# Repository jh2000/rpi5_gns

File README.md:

# RPi5 HAT+ for GNS AIS and ADS-B Modules

# Aktuelle Fehler
- Im aktuellen Layout ist ein Kreuzungsfehler, dadurch wird UART_Rx an Pin 10 vom GNS5851 mit F_ind verbunden.  
Wird die Platine so gefertigt, muss die Verbindung aufgetrennt werden (direkt vor dem GNS5851, zum Glück sehr gut erreichbar) und manuell eine Brücke von Pin 5 zu R7 gelegt werden.
- Der RX-Pin vom AIS-Modul ist mit GPIO 7 anstelle 8 verbunden, daher ist keine Kommunikation vom RPi zum AIS-Modul möglich. Ein Workaround ist, die nebeneinander liegenden Pins GPIO 7 und 8 (Pins 24 und 26) zu verbinden.
- Das Loch der GPS-Antenne ist scheinbar nicht richtig positioniert, es passt aber noch ausreichend gut. Vermutlich sind die Abstandsmaße von der falschen Seite.
- die Adressierung des PCF8574 ist invertiert On=Low.
- die Seitenpins der ADS-B und AIS Empfängers sind gem. Datenblatt angelegt, sie lassen sich aber nur per Heißluft anlöten, da man von der Seite nicht mit einem Lötkolben an die Pins kommt. Dazu sind sie sehr exakt zu positionieren. Am besten zuerst diese 4 anlöten und prüfen ob etwas gebrückt wurde.
- am AIS-Empfänger sind zusätzliche Lötpunkte an den Gehäuseseiten auf der Platine, die sind aber überflüssig. Ebenso werden ohne Daisy-Chaining die 4 Seitenpins nicht benötigt und könnten auch weg bleiben.

# Allgemein
Schaltplan und Platinendesign mit KiCAD 9.0.  
Im Repo zu finden sind die Projektdateien sowie footprints und symbole der Bauteile der Firma GNS.  
Die RPi HAT Footprints und Symbole stammen aus einem anderen Repo, siehe Links.  
Es gibt ebenso eine Adapterplatine um die AIS/ADSB-Platinen mit allen Pins auf eine Pfostenleiste zu bekommen um z.B. einen ESP32/Arduino o.ä. zu verwenden.  
GNS bietet verschiedene Stufen von Features, die Platinen sind Pinkompatibel, somit lassen sich alternativ zum GNS5894T auch GNS5894TAC oder der abgespeckte GNS 5892R verwenden.  
Das GPS-Modul ist nicht Pinkompatibel mit den anderen. Für AIS gibt es zur Zeit nur ein Modul.  
Anstelle eines RPi5 kann weitestgehend auch ein RPi4 verwendet werden. Es gibt aber im Detail Unterschiede zu beachten, auf die ich hier erst mal nicht näher eingehe.

# Pro&Contra
+ \+ CPU quasi idle
+ \+ dadurch wesentlich energieeffizienter gegenüber SDR/DVB-Sticks
+ \+ mehr Platz für SDR für Schiff-&Flugfunk
+ \- hoher Preis
+ \- nicht alle Feeder kompatibel

# Disclaimer
~~Die Designs sind noch ungeprüft und befinden sich zur Zeit in der Platinenfertigung. Es ist daher ein starker 'work in progress' ohne validierte Layouts.~~  
Die Designs habe ich jeweils einmal fertigen lassen. Dabei sind die oben genannten kleineren Fehler aufgefallen. Grundsätzlich funktionieren die Platinen im aktuellen Zustand.  

**Ich bin eine Privatperson und stehe nicht mit Firma GNS, rpi, jlcpcb oder Anderen in kommerzieller Verbindung**  
**Für Schäden übernehme ich keine Haftung**  

# Beschreibung der Platine
Benutzt werden GNS701 als GPS-Empfänger mit PPS Ausgang, GNS5851 als AIS-Empfänger sowie GNS5894T als ADSB Empfänger.  
Des Weiteren sind ein EEPROM für die HAT+ Erkennung, sowie ein I2C GPIO-Expander (PCF8574AT) vorhanden um die Reset/Steuereingänge anzusteuern.  
Die Adresse des GPIO-Expanders kann über DIP-Schalter frei gewählt werden.  
Das EEPROM zur automatschen HAT Erkennung (z.B. CAT24C128) hat Lötpads um den schreibschutz und die Adresse zu steuern. Standardmäßig ist 0x50. Gem. spezifikation würde auch 0x51 gehen.
Sollte das HAT zusammen mit anderen Verwendet werden muss geprüft werden, dass es keinen Konflikt der Adresse oder Pins gibt.
Aus Platz- und Komplexitätsgründen habe ich auf viele Bauteile verzichtet. Entsprechend fehlen Stütz-/Filterkapazitäten, Pegelbegrenzer usw.  
Es lassen sich theoretisch 2 der AIS Empfänger Chips Daisy-Chainen um auf Kanal A und B zeitgleich zu lauschen. Mit mehr Durchkontaktierungen und den Signalteilern/Filtern/Verstärkern gem. Herstellervorgabe könnte es noch knapp auf die Platine drauf passen. 

# Verdrahtung
Der ADSB-Empfänger hängt an UART0. Hier werden die Flusssteuerung über CTS/RTS (GPIO 16/17, Pin 36/11) mit angesteuert.  
Der AIS-Empfänger hängt an UART3.  
Der GPS-Empfänger hängt an UART4, die PPS Funktion an GPIO26/Pin 37.  

# Konfiguration
die HAT+ Erkennung hat zur Zeit keine funktionalen Benefits, daher müssen alle Einstellungen/Programme selbst getätigt/geladen werden.  
Sobald die Hardware lauffähig getestet ist lassen sich zumindest die overlay Anteile und Pinsteuerungen so automatisieren.
Ich verwende Debian 12.

**/boot/config.txt**
```
dtoverlay=pps-gpio,gpiopin=26  
dtoverlay=uart0-pi5,ctsrts  
dtoverlay=uart3-pi5  
dtoverlay=uart4-pi5
dtparam=i2c1=on
dtoverlay=pcf857x,addr=38 # Wohl obsolet
```
**/etc/default/gpsd**
```
DEVICES="/dev/ttyAMA4 /dev/pps0"
GPSD_OPTIONS="-s 9600 -n"
```

**/etc/ntpsec/ntp.conf**
```
server 127.127.22.0 minpoll 4 maxpoll 4
fudge 127.127.22.0 refid PPS
fudge 127.127.22.0 flag3 1 # enable kernel PLL/FLL clock discipline

server 127.127.28.0 minpoll 4 maxpoll 4 prefer # PPS requires at least one preferred peer
fudge 127.127.28.0 refid GPS
fudge 127.127.28.0 time1 +0.130 # coarse offset due to the UART delay

```
**/etc/ser2net.yaml**
```
connection: &adsb01
    accepter: tcp,4000
    enable: on
    options:
      kickolduser: true
    connector: serialdev,/dev/ttyAMA0,3000000n81,local rtscts # Bei Textmodus
    #    921600n81,local rtscts Bei HULC
connection: &ais01
    accepter: tcp,2001
    enable: on
    options:
      kickolduser: true
    connector: serialdev,/dev/ttyAMA3,115200n81,local
connection: &gps01
    accepter: tcp,3002
    enable: on
    options:
      kickolduser: true
    connector: serialdev,/dev/ttyAMA4,9600n81,local

```
# Peripherie
**Steuerchip PCF8574AT**  
Der GPIO-Expander steuert folgende Funktionen:

|Pin|Funktion|Beschreibung|
|-|-|-|
|P0|ADS-B Reset|low für reset des GNS5894T Receivers, float/high für Betrieb|
|P1|ADS-B Modus|wenn J3 auf 2-3 gebrückt, steuerung des Modus (float/high=Text, low=Binär)
|P2|GPS Reset|low für reset des GNS701 Receivers, float/high für Betrieb|
|P3|GPS Enable|float/high um GNS701 zu aktivieren, low für Standby|
|P4|AIS Reset|low für reset des GNS5851 Receivers, float/high für Betrieb|
|P5|NC|Nicht verbunden|
|P6|NC|Nicht verbunden|
|P7|NC|Nicht verbunden|

Die Adresse des GPIO-Expanders kann über den Dipschalter SW1 zwischen 0x38 und 0x3F frei eingestellt werden.  
Zu beachten ist, dass die DIP-Switche gegen Masse schalten, also On = Masse. Entsprechend ist alle auf On = 0x38 und alle auf Off = 0x3F!

**AIS Modul GNS5851**  
Das AIS-Modul verwendet 115200-8-N-1 für die serielle Kommunikation.  
Beim Power on oder sobald das Modul resetet wird, wird die Version ausgeben:  
$PGNS,0,V,GNS5851,23.20.1,1.0-1,H,S01*08

Es gibt folgende Befehle auf die reagiert wird, jeweils im NMEA 0183 Standard:
Versionsabfrage, $PGNS,V*70<CR><LF>  
Betriebsmodus, $PGNS,M,A*06, $PGNS,M,B*07 oder $PGNS,M,H*0D für nur Kanal *A*, nur *B* oder Kanal*H*opping.  
Nach einem Reset wird die Version ausgegeben.  

**ADS-B Modul GNS5894TAC**  
DAS ADS-B Modul verwendet je nach Einstellung HULC oder Textprotokoll für die ADS-B Daten mit entsprechend 921600 oder 3000000 Baud, je 8 N 1.  
Aufgrund der Datenrate ist die Verwendung von RTS/CTS Handshakes empfohlen.  
Im HULC Modus wird sekündlich ein Datenpaket übertragen, im Textmodus dagegen gibt es abseits empfangener Signale keinerlei Status, auch nicht beim Reset/Einschalten.  
Die Funktionsfähigkeit kann hier getestet werden indem "#00" gesendet wird.

Das Modul empfängt auf dem 2. UART Port die GPS Daten vom GNS701 und erwartet diese mit 9600 Baud und einer Position pro Sekunde. Benutzt wird dafür der 2. Ausgang des GPS-Empfängers.

Es gibt folgende Befehle, je nach Protokoll:
Versionsabfrage, #00<CR><LF>  
Betriebsmodus abfragen, #43<CR><LF>  
Betriebsmodus setzen, #43-XY<CR><LF> wobei X 1 für MLAT sowie 8 für RSSI ist und Y die Ausgabe steuert (0 Mode S off, 1 'reserved, do not use', 2 Output all Mode-S  & Mode-A/C data, default, 3 nur ADS-B und 4 nur ADS-B mit gültigem CRC)  
Reset, #FF<CR><LF>  

**GPS Modul GNS701**  
Bei der Konfiguration des GPS-Empfängers zu beachten, dass die Daten des 2. Ausganges (TX1) an das ADS-B Modul gehen.  
Standardmäßig werden 9600 Baud, 8-N-1 mit einer Position pro Sekunde  benutzt für beide Schnittstellen.  
Solange das Modul im Reset oder Standby zustand ist, bleibt die 3D-Fix LED aus. Solange das Modul ansonsten im Normalbetrieb ist, sollte mindestens einmal pro Sekunde etwas im Terminal zu finden sein, im Takt mit dem Blinken der 3D-Fix LED.

Die Konfiguration basiert auf der MediaTek Befehlsreferenz. Entsprichend sollten die dortigen Befehle gehen  
Testpaket: $PMTK000*32<CR><LF>  
Versionsabfrage: $PMTK604*6D<CR><LF>  

**Allgemein**  
Die Module geben über die UART-Schnittstelle standardmäßig (lesbaren) Text aus. Es kann für ADS-B aber auch das HULC/Beast Binärformat anstelle von AVR benutzt werden.
Alle üblichen Programme können die Daten entsprechend lesen, bis auf modesdeco2, welches nur Funkrohdaten verarbeiten kann.  

Erfolgreich getestete feeder für AIS mit dem GNS5851:  
+ sxfeeder
+ AIS-Catcher

Erfolgreich getestete feeder für ADS-B mit dem GNS5894T:  
+ rbfeeder (radarbox)
+ feed-adsbx (adsbexchange)
+ mlat-client (adsbexchange)
+ fr24feed (flightradar)

Das GPS-Modul bietet GPS und PPS Daten für z.B. gpsd.  

In der Zielarchitektur verwende ich gpsd, ser2net und alle Feeder der jeweiligen Platformen.  
Dabei werden die AIS und ADS-B rohdaten via ser2net vom jeweiligen primärprogramm (AIS-Catcher, rbfeeder) gelesen und stellen diese Daten dann an sekundärfeeder (sxfeeder, feed-adsb usw...) bereit.
ser2net hat sich als praktisch erwiesen, da es sich einfach debuggen lässt indem man z.b. per nc oder telnet verbinden kann.  
gpsd und ntpd stellen dem System die genauen Zeitdaten bereit. Wer es richtig übertreiben will, kann das Design anpassen und einen RTK fähigen GPS Empfänger einbauen.

Das HAT sollte HAT+ Spezifikationen erfüllen, dies ist aber noch nicht bestätigt, im Design ist testweise ein HAT+ Logo angebracht.

Im aktuellen Design gegenüber dem Referenzentwurf fehlt der Schlitz um an einen der CSI Ports zu kommen. Da dies ggf. Bestandteil der HAT+ Hardwareforderungen ist, muss dies noch korrigiert werden.  
Diese Abweichung zeigt KiCAD entsprechend als Warnung an.  
Des Weiteren werden die je 4 zusätzlichen Pads der AIS und ADS-B Module als zu eng für die Standardabstände geflaggt. Somit sollten anfangs 1+3+3 Warnungen bzw. Fehler auftreten, welche ignoriert werden können.

# Linksammlung:

+ HAT+ Spezifikation: [https://datasheets.raspberrypi.com/hat/hat-plus-specification.pdf]
+ GPS: [https://www.gns-electronics.de/product/gns-701/]
+ AIS: [https://www.gns-electronics.de/product/gns-5851-ais-module/]
+ AIS Daisy-Chaining: [https://www.gns-electronics.de/wp-content/uploads/2025/05/GNS5851_AppNote_2ch-Receiver-V0.9.pdf]
+ ADS-B: [https://www.gns-electronics.de/product/gns-5894-highperformance-ads-b-modul/]
+ RPi HAT Template: [https://github.com/devbisme/RPi_Hat_Template]
+ Prototypenfertiger: [https://jlcpcb.com/]
+ PMTK Protokoll: [https://cdn.sparkfun.com/assets/f/0/9/1/c/PMTK_Protocol.pdf]

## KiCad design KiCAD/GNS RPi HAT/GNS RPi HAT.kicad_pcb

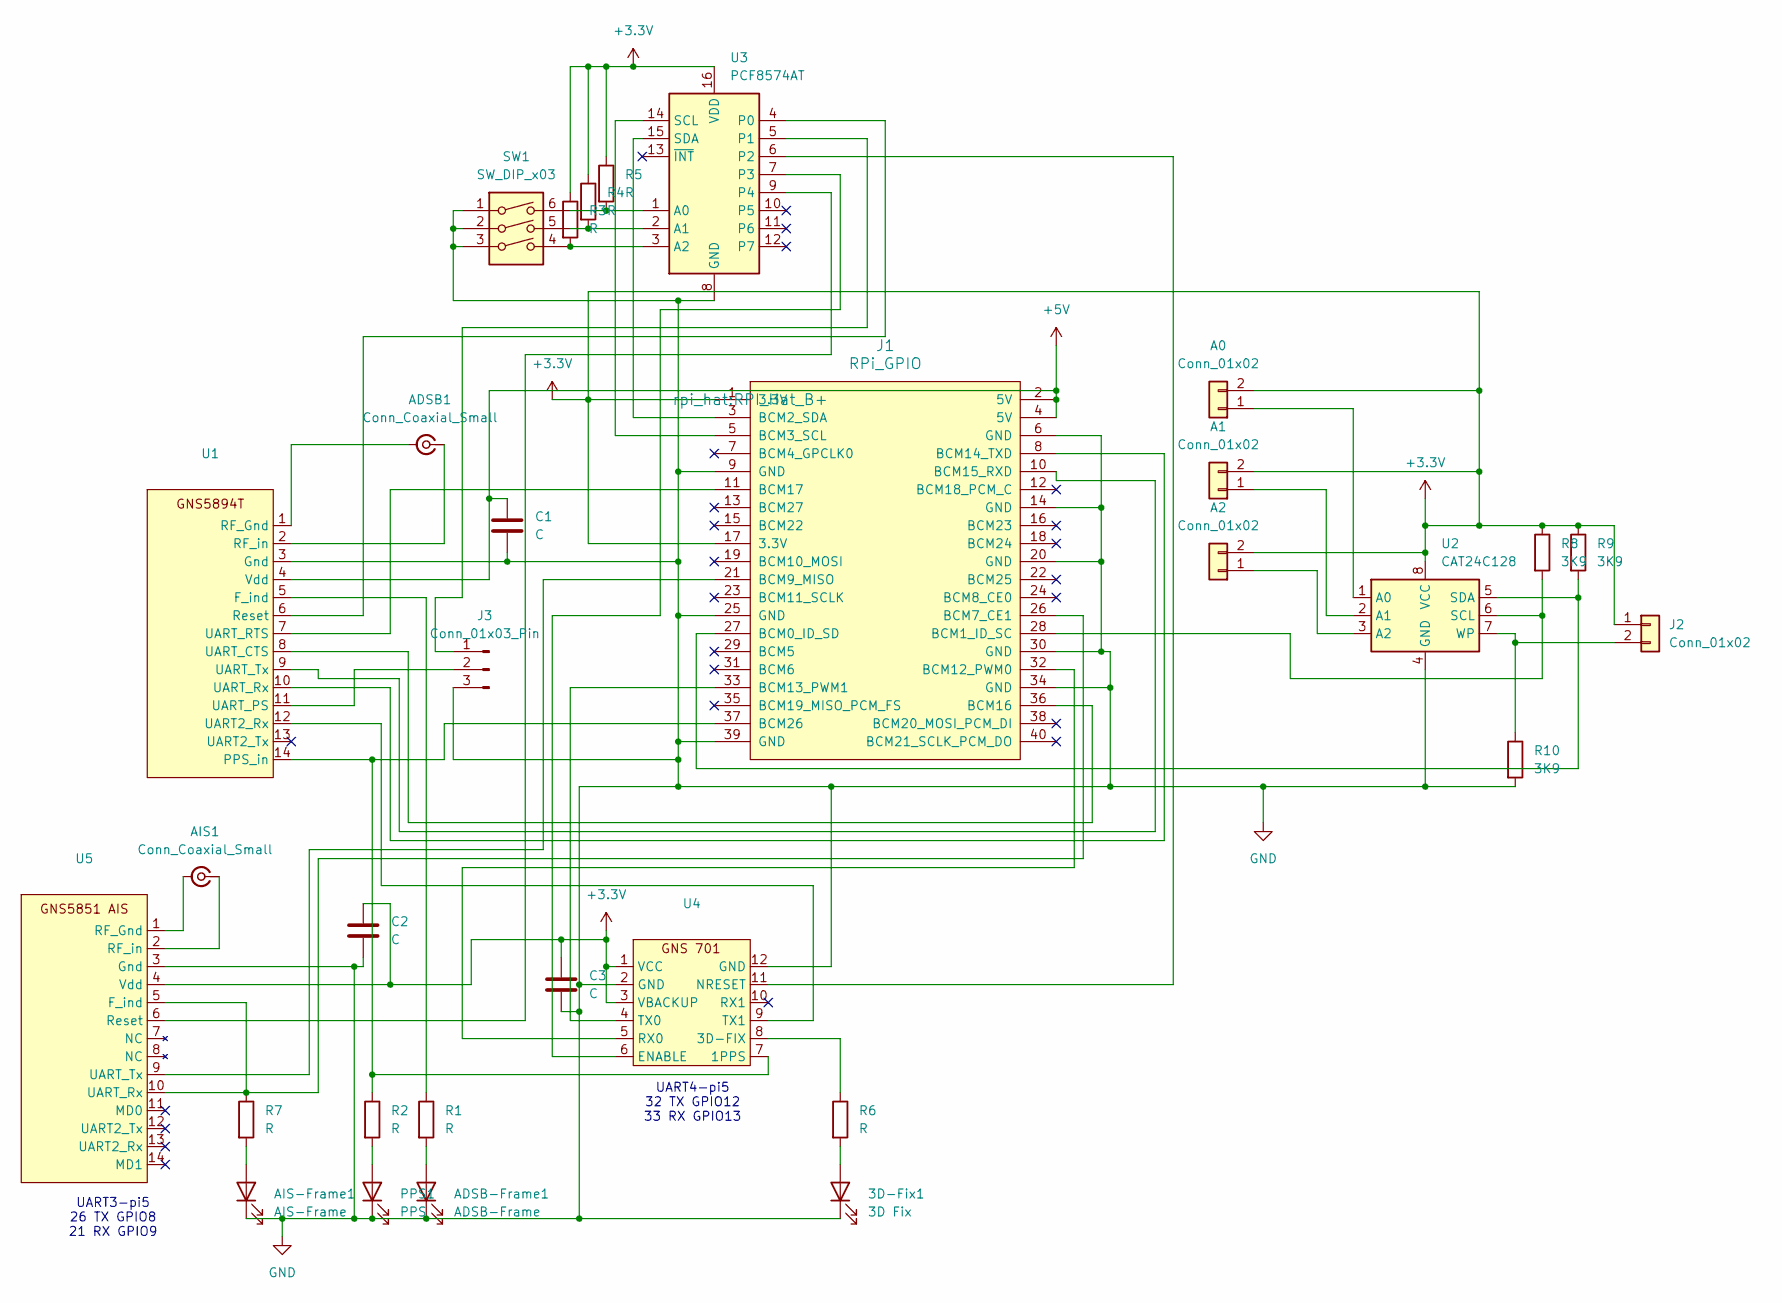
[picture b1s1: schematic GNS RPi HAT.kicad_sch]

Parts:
3D-Fix1: 3D Fix; LED_0805_2012Metric_Pad1.15x1.40mm_HandSolder
A0, A1, A2: Conn_01x02; SolderJumper-2_P1.3mm_Open_Pad1.0x1.5mm
ADSB1: Conn_Coaxial_Small; SMA_Amphenol_901-144_Vertical
ADSB-Frame1: ADSB-Frame; LED_0805_2012Metric_Pad1.15x1.40mm_HandSolder
AIS1: Conn_Coaxial_Small; SMA_Amphenol_901-144_Vertical
AIS-Frame1: AIS-Frame; LED_0805_2012Metric_Pad1.15x1.40mm_HandSolder
C1, C2, C3: C; C_0805_2012Metric_Pad1.18x1.45mm_HandSolder
J1: RPi_GPIO; RPI_Hat_B+
J2: Conn_01x02; PinSocket_1x02_P2.54mm_Vertical
J3: Conn_01x03_Pin; PinHeader_1x03_P2.54mm_Vertical
PPS1: PPS; LED_0805_2012Metric_Pad1.15x1.40mm_HandSolder
R1, R2, R3, R4, R5, R6, R7: R; R_0805_2012Metric_Pad1.20x1.40mm_HandSolder
R8, R9, R10: 3K9; R_0805_2012Metric_Pad1.20x1.40mm_HandSolder
SW1: SW_DIP_x03; SW_DIP_SPSTx03_Slide_9.78x9.8mm_W7.62mm_P2.54mm
U1: GNS5894T
U2: CAT24C128; SOIC-8_3.9x4.9mm_P1.27mm
U3: PCF8574AT; SOIC-16W_7.5x10.3mm_P1.27mm
U4: GNS701
U5: GNS5851

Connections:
+3.3V: A0.2, A1.2, A2.2, C2.1, C3.1, J1.1 (3.3V), J1.17 (3.3V), J2.1, R3.1, R4.1, R5.1, R8.1, R9.1, U2.8 (VCC), U3.16 (VDD), U4.1 (VCC), U4.3 (VBACKUP), U5.4 (Vdd)
+5V: C1.1, J1.2 (5V), J1.4 (5V), U1.4 (Vdd)
GND: 3D-Fix1.1 (K), ADSB-Frame1.1 (K), AIS-Frame1.1 (K), C1.2, C2.2, C3.2, J1.6 (GND), J1.9 (GND), J1.14 (GND), J1.20 (GND), J1.25 (GND), J1.30 (GND), J1.34 (GND), J1.39 (GND), J3.3, PPS1.1 (K), R10.2, SW1.1, SW1.2, SW1.3, U1.3 (Gnd), U2.4 (GND), U3.8 (GND), U4.2 (GND), U4.12 (GND), U5.3 (Gnd)
unnamed: 3D-Fix1.2 (A), R6.2
unnamed: A0.1, U2.1 (A0)
unnamed: A1.1, U2.2 (A1)
unnamed: A2.1, U2.3 (A2)
unnamed: ADSB1.2 (Ext), U1.1 (RF_Gnd)
unnamed: ADSB1.1 (In), U1.2 (RF_in)
unnamed: ADSB-Frame1.2 (A), R1.2
unnamed: AIS1.2 (Ext), U5.1 (RF_Gnd)
unnamed: AIS1.1 (In), U5.2 (RF_in)
unnamed: AIS-Frame1.2 (A), R7.2
unnamed: J1.27 (BCM0_ID_SD), R9.2, U2.5 (SDA)
unnamed: J1.28 (BCM1_ID_SC), R8.2, U2.6 (SCL)
unnamed: J1.3 (BCM2_SDA), U3.15 (SDA)
unnamed: J1.5 (BCM3_SCL), U3.14 (SCL)
unnamed: J1.26 (BCM7_CE1), R7.1, U5.5 (F_ind), U5.10 (UART_Rx)
unnamed: J1.21 (BCM9_MISO), U5.9 (UART_Tx)
unnamed: J1.32 (BCM12_PWM0), U4.5 (RX0)
unnamed: J1.33 (BCM13_PWM1), U4.4 (TX0)
unnamed: J1.8 (BCM14_TXD), U1.10 (UART_Rx)
unnamed: J1.10 (BCM15_RXD), U1.9 (UART_Tx)
unnamed: J1.36 (BCM16), U1.8 (UART_CTS)
unnamed: J1.11 (BCM17), U1.7 (UART_RTS)
unnamed: J1.37 (BCM26), R2.1, U1.14 (PPS_in), U4.7 (1PPS)
unnamed: J2.2, R10.1, U2.7 (WP)
unnamed: J3.1, U3.5 (P1)
unnamed: J3.2, U1.11 (UART_PS)
unnamed: PPS1.2 (A), R2.2
unnamed: R1.1, U1.5 (F_ind)
unnamed: U1.6 (Reset), U3.4 (P0)
unnamed: U1.12 (UART2_Rx), U4.9 (TX1)
unnamed: R5.2, SW1.6, U3.1 (A0)
unnamed: R4.2, SW1.5, U3.2 (A1)
unnamed: R3.2, SW1.4, U3.3 (A2)
unnamed: U3.6 (P2), U4.11 (NRESET)
unnamed: U3.7 (P3), U4.6 (ENABLE)
unnamed: U3.9 (P4), U5.6 (Reset)
unnamed: R6.1, U4.8 (3D-FIX)

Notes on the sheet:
UART4-pi5 32 TX GPIO12 33 RX GPIO13
UART3-pi5 26 TX GPIO8 21 RX GPIO9

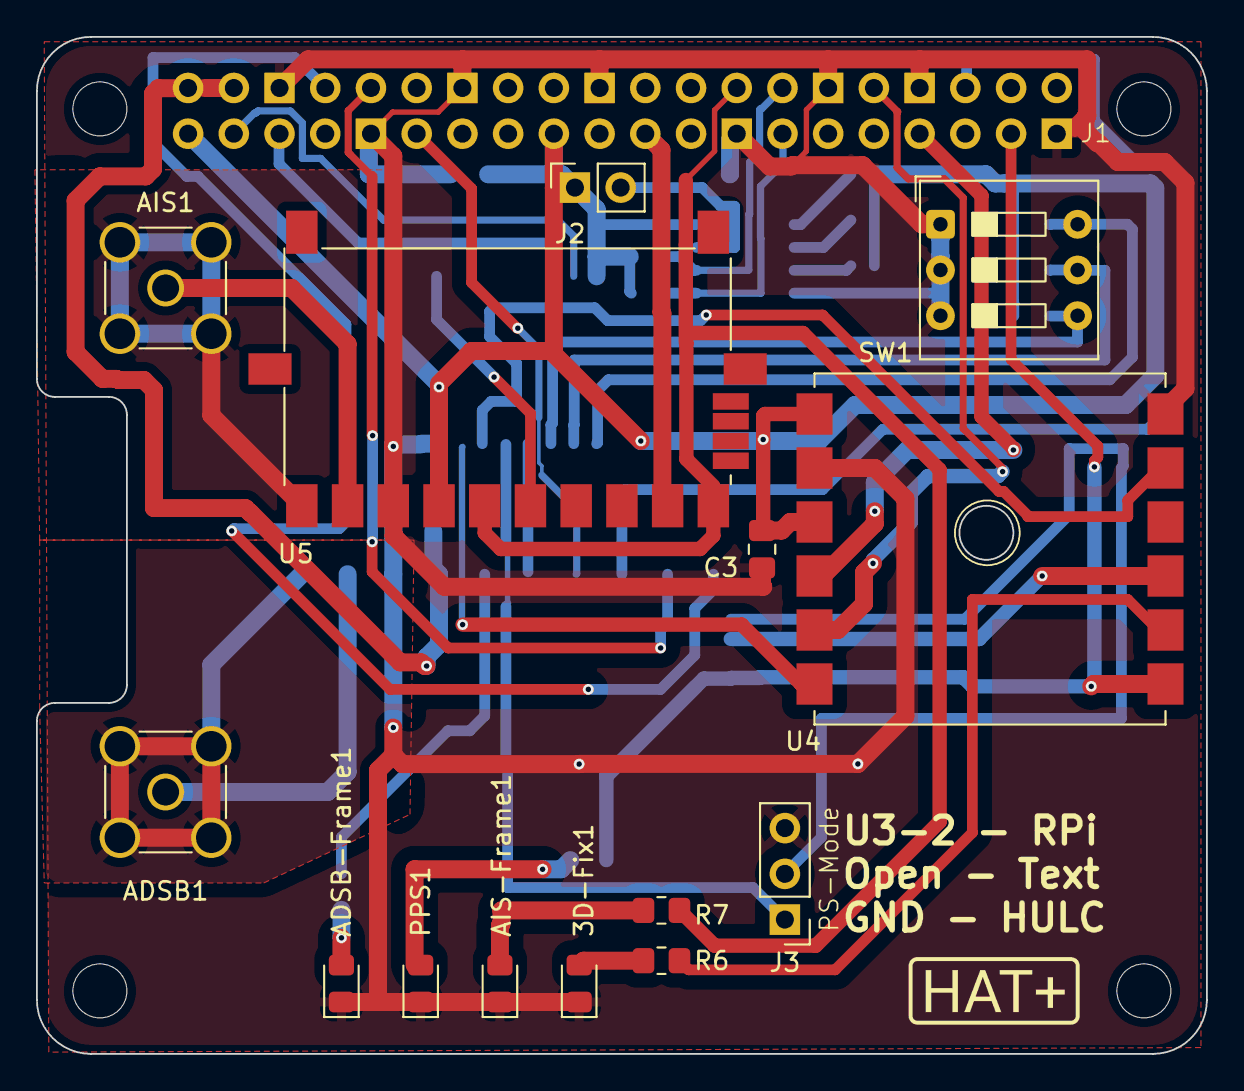
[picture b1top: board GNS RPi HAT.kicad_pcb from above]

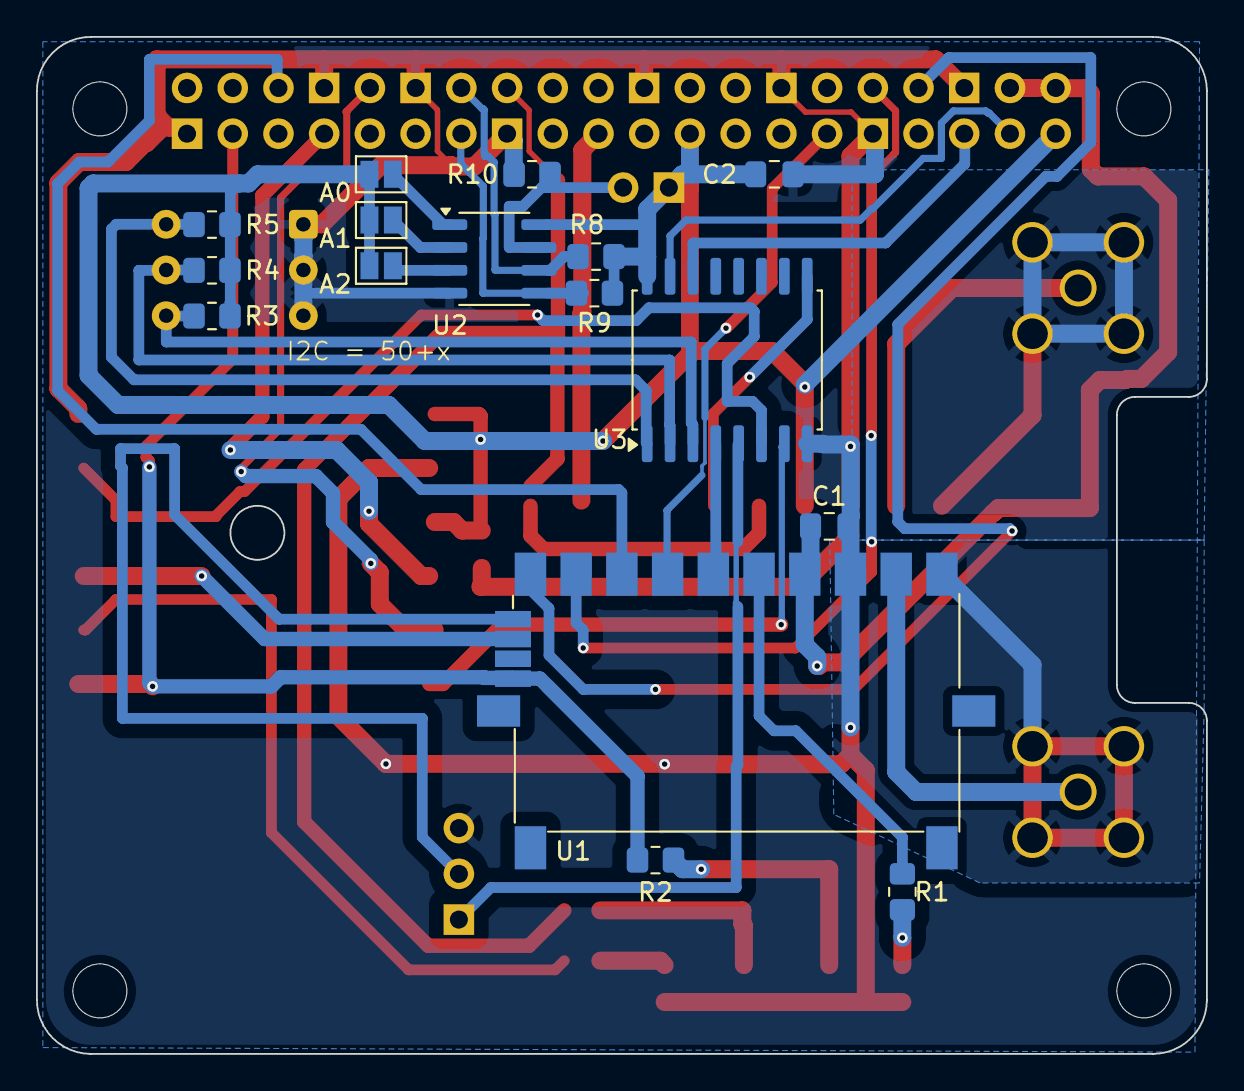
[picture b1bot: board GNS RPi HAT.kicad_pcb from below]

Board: 2 copper layers, 65.0 x 56.5 mm, 31 parts (16 on the bottom side), 40 nets.

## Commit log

2025-08-02 Wechsel auf SMD-Bauteile, Fehlerkorrekturen
    Die Widerstände und Leds wurden auf noch von Hand Lötbare SMD-Varianten geändert.
    Die Platine wurde weiter aufgeräumt.
    Wichtigste Änderung: die Adressierung des I2C Busses für die HAT+ Erkennung wurde von einer fixen Adresse auf Lötpads geändert.
    Die Adressen 0x50, 0x51 und ggf. später weitere sind nun möglich um im Abhängigkeit zu anderen HAT keinen Adresskonflikt zu verursachen.
    Das erste Design hatte noch fix die Adresse 0x5F, welcher in der Spec nicht automatisch erkannt wird.
    Der Schreibschutz ist ebenfalls über eine Lötbrücke steuerbar.
2025-08-02 Update README.md
    Fehlerkorrekturen, Anpassungen der HAT+ Erkennung.
2025-08-02 Update README.md
    Anpassung an aktuellen Erkenntnisstand.
    - Aufnahme der GPIO-Expander Pins
    - Aufnahme der Schnittstellenparameter
2025-08-08 Update README.md
    Erkenntnisse der ersten Fertigungscharge eingearbeitet.
    Prototypplatine funktioniert Grundsätzlich, es sind aber ein paar nacharbeiten zur Korrektur eines Fehlers notwendig.
2025-08-09 Update README.md
    Weiterer Fehler im Design zum AIS-RX Pin.
